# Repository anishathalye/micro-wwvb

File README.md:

# &mu;WWVB: a tiny wwvb station

&mu;WWVB is a watch stand that automatically sets the time on atomic wristwatches where regular [WWVB] signal isn’t available. The system acquires the correct time via GPS and sets radio-controlled clocks by emulating the amplitude-modulated WWVB time signal.

For more information, see [the blog post][micro-wwvb-post].

[WWVB]: https://www.nist.gov/pml/time-and-frequency-division/radio-stations/wwvb
[micro-wwvb-post]: https://www.anishathalye.com/2016/12/26/micro-wwvb/

## Software

Software is in the `src/` directory. If you're using macOS to build the firmware image, use [CrossPack].

[Crosspack]: https://www.obdev.at/products/crosspack/index.html

## Electronics

The board design is in the `board/` directory. `microwwvb.brd` and `microwwvb.sch` are the [Autodesk EAGLE] board and schematic. This directory also contains images of the board outline, traces, schematic, and assembled board.

[Autodesk EAGLE]: https://www.autodesk.com/products/eagle/free-download

### BOM

- [ATtiny44A](https://www.microchip.com/en-us/product/ATtiny44A) microcontroller
- [USGlobalSat EM-506](https://web.archive.org/web/20230314174108/https://www.sparkfun.com/products/12751) GPS receiver
- 20 MHz crystal oscillator ([644-1039-1-ND](https://www.digikey.com/en/products/detail/ndk-nihon-dempa-kogyo-co-ltd/LNCD1-20M/1128821))
- LEDs
    - Red ([67-1356-1-ND](https://www.digikey.com/en/products/detail/lumex-opto-components-inc/SML-LX1206IC-TR/229140))
    - Green ([67-1357-1-ND](https://www.digikey.com/en/products/detail/lumex-opto-components-inc/SML-LX1206GC-TR/229139))
    - Blue ([732-4989-1-ND](https://www.digikey.com/en/products/detail/w%C3%BCrth-elektronik/150120BS75000/4489933))
- Resistors
    - 499 &Omega; ([311-499FRCT-ND](https://www.digikey.com/en/products/detail/yageo/RC1206FR-07499RL/728944))
    - 1 k&Omega;, quantity 2 ([311-1.00KFRCT-ND](https://www.digikey.com/en/products/detail/yageo/RC1206FR-071KL/728387))
    - 10 k&Omega; ([311-10.0KFRCT-ND](https://www.digikey.com/en/products/detail/yageo/RC1206FR-0710KL/728483))
- Capacitors
    - 10 pF, quantity 2 ([311-1150-1-ND](https://www.digikey.com/en/products/detail/yageo/CC1206JRNPO9BN100/302884))
    - 1 &mu;F ([445-1423-1-ND](https://www.digikey.com/en/products/detail/tdk-corporation/C3216X7R1H105K160AB/569049))
- Mini USB connector ([H2961CT-ND](https://www.digikey.com/en/products/detail/hirose-electric-co-ltd/UX60A-MB-5ST/597537))
- [JST horizontal 6-Pin connector](https://www.sparkfun.com/jst-sh-horizontal-6-pin-connector-smd.html)
- Pin headers
    - 4-pin ([609-5160-1-ND](https://www.digikey.com/en/products/detail/amphenol-cs-fci/95278-801A04LF/1535898))
    - 6-pin ([609-5161-1-ND](https://www.digikey.com/en/products/detail/amphenol-cs-fci/95278-801A06LF/1535720))

## Enclosure

The CAD files for the physical enclosure are in the `cad/` directory. The top and bottom pieces of the &mu;WWVB station are 3D-printed, and the sides are laser-cut acrylic.

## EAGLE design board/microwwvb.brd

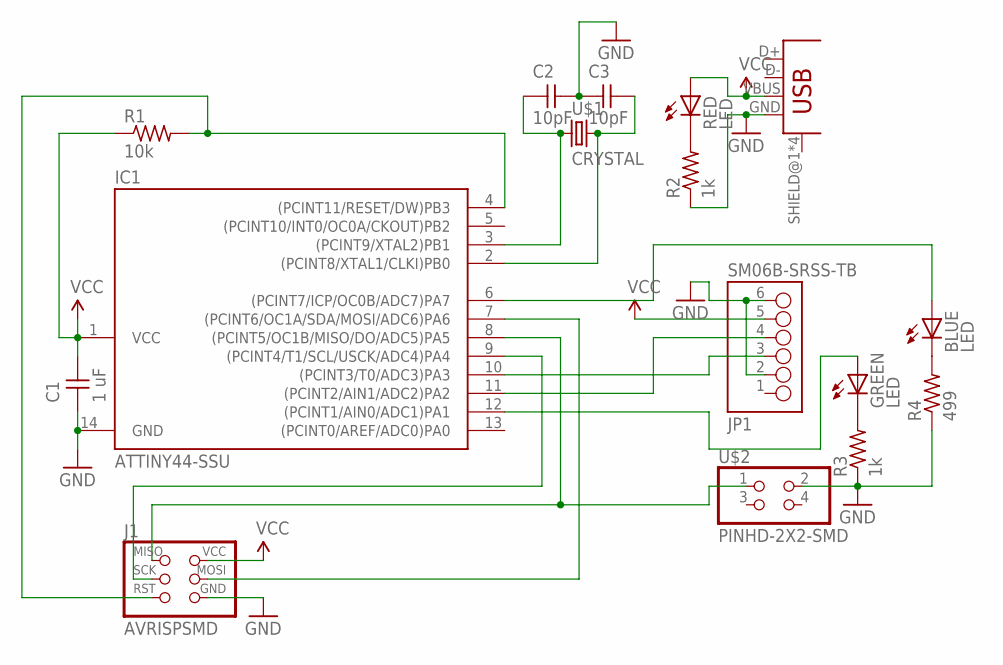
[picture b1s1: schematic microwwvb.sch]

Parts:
BLUE: LED; LED1206
C1: 1 uF; C1206
C2, C3: 10pF; C1206
GREEN: LED; LED1206
IC1: ATTINY44-SSU; SOIC14
J1: AVRISPSMD; 2X03SMD
JP1: SM06B-SRSS-TB
R1: 10k; R1206
R2, R3: 1k; R1206
R4: 499; R1206
RED: LED; LED1206
U$1: CRYSTAL; 2-SMD-5X3MM
U$2: PINHD-2X2-SMD; 2X02SMD
U$3: USB_MINIB

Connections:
GND: C1.1, C2.2, C3.1, IC1.14 (GND), J1.6 (GND), JP1.2, JP1.6, R2.1, R3.1, R4.1, U$2.2, U$3.GND
unnamed: C3.2, IC1.2 ((PCINT8/XTAL1/CLKI)PB0), U$1.P$2 (2)
unnamed: C2.1, IC1.3 ((PCINT9/XTAL2)PB1), U$1.P$1 (1)
unnamed: IC1.4 ((PCINT11/RESET/DW)PB3), J1.5 (RST), R1.2
unnamed: IC1.8 ((PCINT5/OC1B/MISO/DO/ADC5)PA5), J1.1 (MISO), U$2.1
unnamed: IC1.7 ((PCINT6/OC1A/SDA/MOSI/ADC6)PA6), J1.4 (MOSI)
unnamed: R2.2, RED.2 (C)
unnamed: GREEN.2 (C), R3.2
unnamed: IC1.10 ((PCINT3/T0/ADC3)PA3), JP1.3
unnamed: IC1.9 ((PCINT4/T1/SCL/USCK/ADC4)PA4), J1.3 (SCK)
unnamed: IC1.11 ((PCINT2/AIN1/ADC2)PA2), JP1.4
unnamed: GREEN.1 (A), IC1.12 ((PCINT1/AIN0/ADC1)PA1)
unnamed: BLUE.2 (C), R4.2
unnamed: BLUE.1 (A), IC1.6 ((PCINT7/ICP/OC0B/ADC7)PA7)
VCC: C1.2, IC1.1 (VCC), J1.2 (VCC), JP1.5, R1.1, RED.1 (A), U$3.VBUS

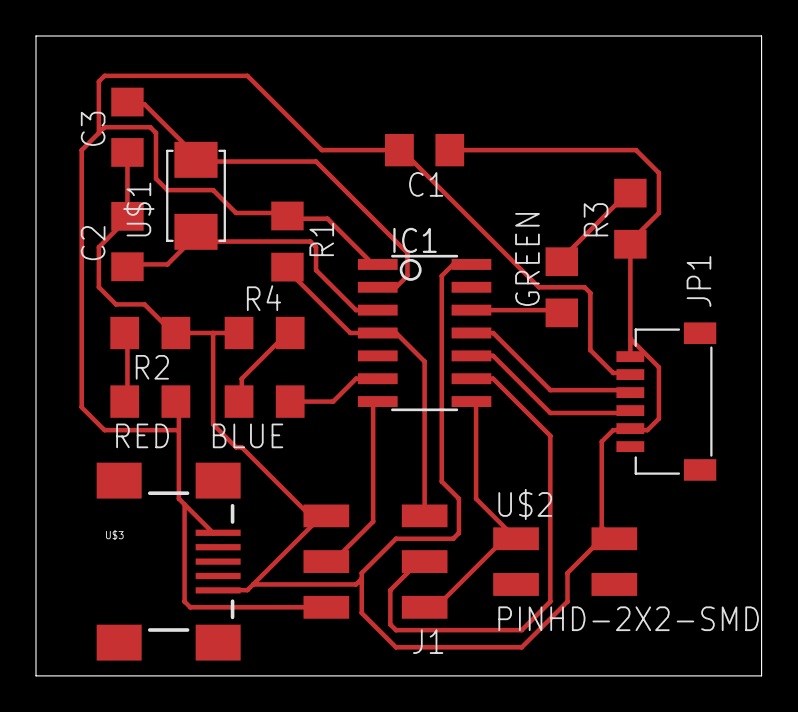
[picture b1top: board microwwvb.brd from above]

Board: 2 copper layers, 40.3 x 35.5 mm, 16 parts (0 on the bottom side), 15 nets.

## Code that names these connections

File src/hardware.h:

#ifndef HARDWARE_H
#define HARDWARE_H

#include "serial.h"
#include <avr/io.h>

#define GPS_BAUD_RATE BAUD_RATE_4800
#define GPS_PORT PORTA
#define GPS_PORT_DDR DDRA
#define GPS_PORT_NUM PA2
#define GPS_PIN PINA
#define GPS_PIN_DDR DDRA
#define GPS_PIN_NUM PB3

#define LED_G_PORT PORTA
#define LED_G_PORT_DDR DDRA
#define LED_G_PORT_NUM PA1
#define LED_B_PORT PORTA
#define LED_B_PORT_DDR DDRA
#define LED_B_PORT_NUM PA7

#endif // HARDWARE_H

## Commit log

2017-05-14 Enable link-time optimization
2018-09-11 Make function static inline
2019-02-22 Add outline
2022-07-20 Add license
2022-07-20 Add brief description and image to README
2023-03-05 Remove copyright years
2025-08-02 Add EAGLE board and schematic
2025-08-02 Add BOM

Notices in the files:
parts and their libraries:
SparkFun-Aesthetics: Licensing: Creative Commons ShareAlike 4.0 International - https://creativecommons.org/licenses/by-sa/4.0
